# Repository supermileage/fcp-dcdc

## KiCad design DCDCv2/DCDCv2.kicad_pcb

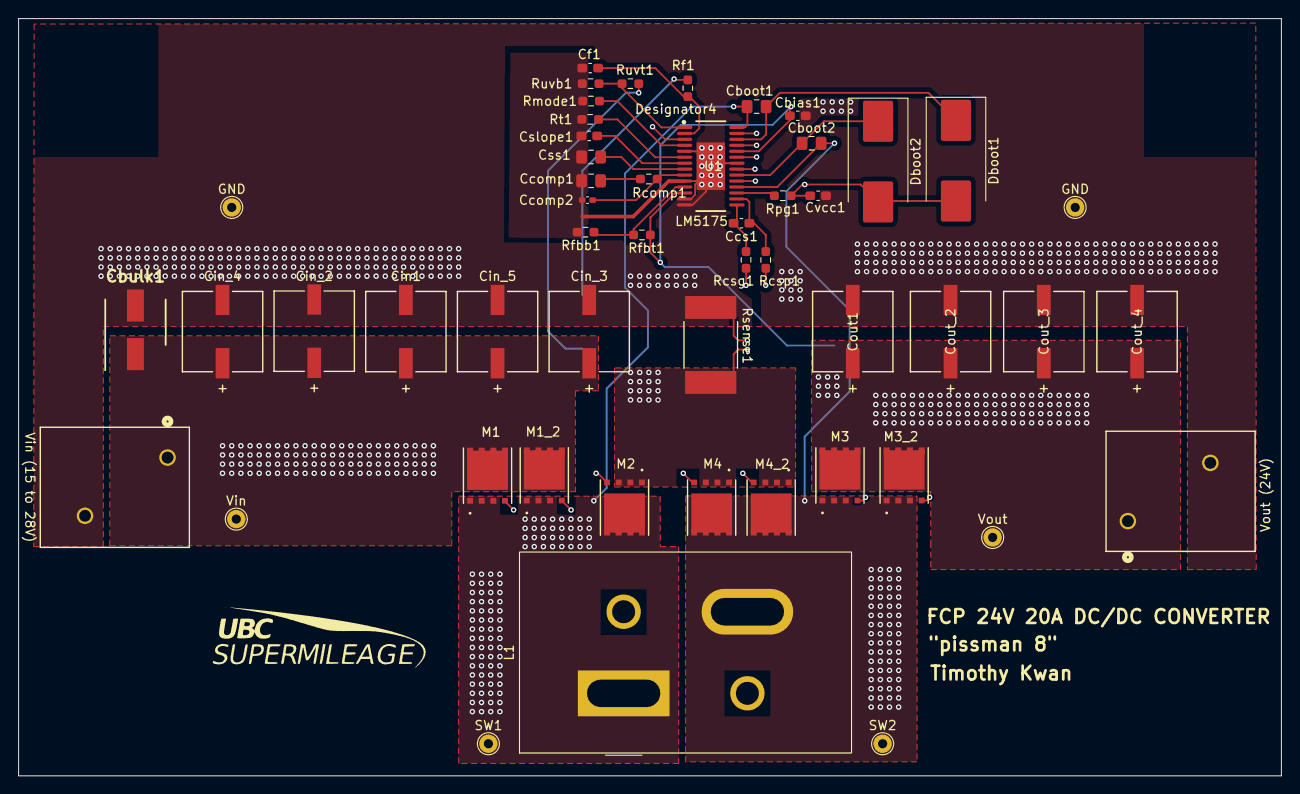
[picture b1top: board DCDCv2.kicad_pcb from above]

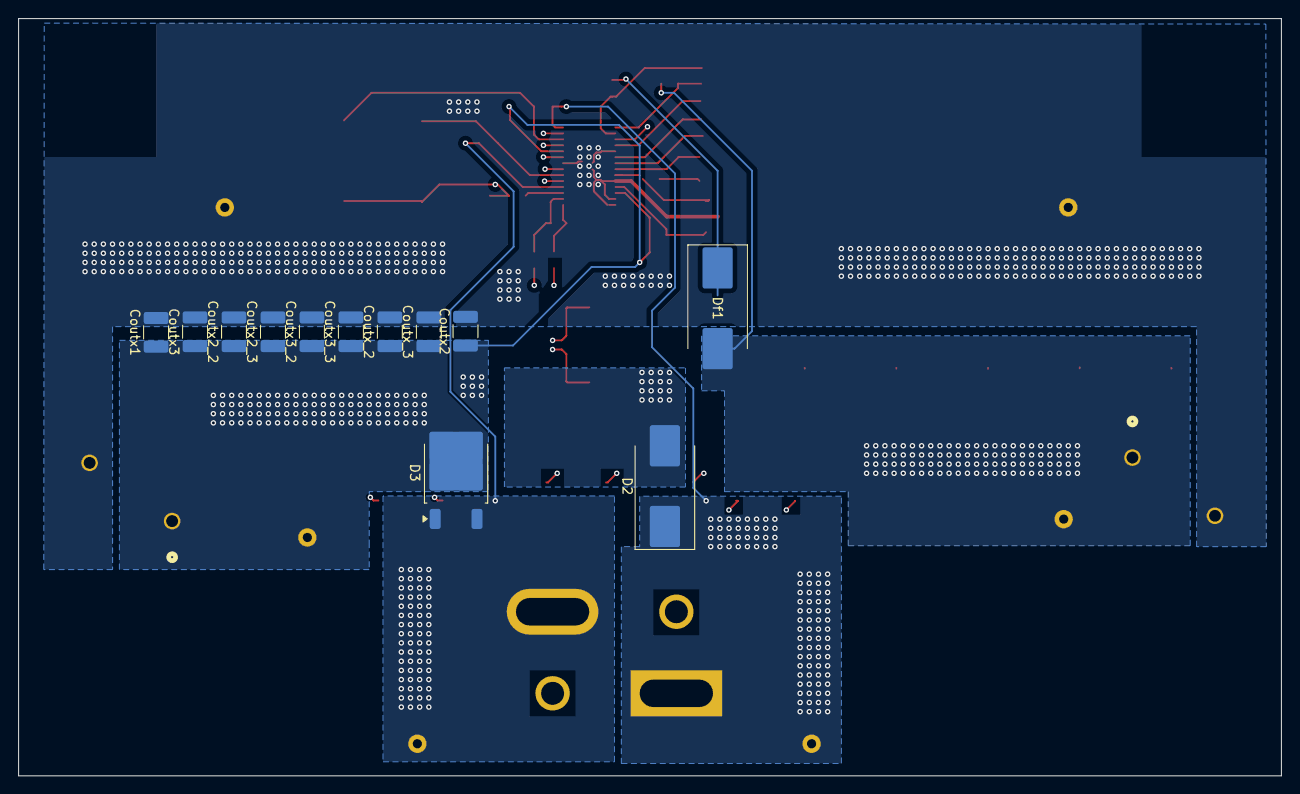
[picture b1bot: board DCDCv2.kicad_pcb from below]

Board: 4 copper layers, 137.8 x 82.6 mm, 63 parts (12 on the bottom side), 26 nets.

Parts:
Cbias1: C1608X5R1H105K080AB; C_0603_1608Metric_Pad1.08x0.95mm_HandSolder
Cboot1, Cboot2: 08053C104JAZ2A; C_0805_2012Metric_Pad1.18x1.45mm_HandSolder
Cbulk1: UUD1V680MCL1GS; CAPAE660X800N
Ccomp1: C2012C0G1H153J085AA; C_0805_2012Metric_Pad1.18x1.45mm_HandSolder
Ccomp2: CL05C681JB5NNNC; C_0402_1005Metric_Pad0.74x0.62mm_HandSolder
Ccs1: 06035A470JAT2A; C_0603_1608Metric_Pad1.08x0.95mm_HandSolder
Cf1: C1608X5R1H224K080AB; C_0603_1608Metric_Pad1.08x0.95mm_HandSolder
Cin1: 50SVPF39M; PCAP_SVP_E12_PAN
Cin_2, Cin_3, Cin_4, Cin_5: 50SVPF39M; PCAP_SVP_E12_PAN
Cout1: 35SVPF82M
Cout_2, Cout_3, Cout_4: 35SVPF82M
Coutx1, Coutx3, Coutx3_2, Coutx3_3: GRM32ER71H106MA12; C_1210_3225Metric_Pad1.33x2.70mm_HandSolder
Coutx2, Coutx2_2, Coutx2_3: C5750X7R2E684M; C_1210_3225Metric_Pad1.33x2.70mm_HandSolder
Coutx_2, Coutx_3: GRM32ER71H106MA12; C_1210_3225Metric_Pad1.33x2.70mm_HandSolder
Cslope1: CL10C151JB8NNNC; C_0603_1608Metric_Pad1.08x0.95mm_HandSolder
Css1: CGA4J2C0G1H223J125AA; C_0805_2012Metric_Pad1.18x1.45mm_HandSolder
Cvcc1: EMK107B7105KA-T; C_0603_1608Metric_Pad1.08x0.95mm_HandSolder
D2: SL44-E3/57T; D_SMC_Handsoldering
D3: SBRD10200TR; TO-252-2
Dboot1, Dboot2: SL44-E3/57T; D_SMC_Handsoldering
Df1: SL44-E3/57T; D_SMC_Handsoldering
GND: TestPoint_THTPad_D2.0mm_Drill1.0mm
GND#2: TestPoint_THTPad_D2.0mm_Drill1.0mm
L1: GENERIC_INDUCTOR; L_Wurth_WE-HCFT-3521
M1, M1_2: CSD18513Q5A; 8power tdfn
M2: CSD18531Q5A; 8power tdfn
M3, M3_2: CSD18533Q5A; 8power tdfn
M4, M4_2: CSD19534Q5A; 8power tdfn
Rcomp1: CRCW04024K99FKED; R_0603_1608Metric_Pad0.98x0.95mm_HandSolder
Rcsg1: CRCW0603100RFKEA; R_0603_1608Metric_Pad0.98x0.95mm_HandSolder
Rcsp1: CRCW0603100RFKEA; R_0603_1608Metric_Pad0.98x0.95mm_HandSolder
Rf1: RC0603FR-0710RL; R_0603_1608Metric_Pad0.98x0.95mm_HandSolder
Rfbb1: RC0603FR-0720KL; R_0603_1608Metric_Pad0.98x0.95mm_HandSolder
Rfbt1: RC0603FR-07576KL; R_0603_1608Metric_Pad0.98x0.95mm_HandSolder
Rmode1: RC0603FR-0793K1L; R_0603_1608Metric_Pad0.98x0.95mm_HandSolder
Rpg1: RC0603FR-0720KL; R_0603_1608Metric_Pad0.98x0.95mm_HandSolder
Rsense1: CUSTOM2; RES_WSLP3921_.002OHM_VIS
Rt1: CRCW0402267KFKED; R_0603_1608Metric_Pad0.98x0.95mm_HandSolder
Ruvb1: RC0201FR-0723K7L; R_0603_1608Metric_Pad0.98x0.95mm_HandSolder
Ruvt1: RC0201FR-07249KL; R_0603_1608Metric_Pad0.98x0.95mm_HandSolder
SW1, SW2: TestPoint_THTPad_D2.0mm_Drill1.0mm
U1: LM5175PWPR; PWP0028F_N
Vin: TestPoint_THTPad_D2.0mm_Drill1.0mm
Vin (15 to 28V): Screw_Terminal_01x02; CONN_1777545
Vout: TestPoint_THTPad_D2.0mm_Drill1.0mm
Vout (24V): Screw_Terminal_01x02; CONN_1777545

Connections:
/hdrv1: M1.4 (Gate), M1_2.4 (Gate), U1.27 (HDRV1)
/hdrv2: M3.4 (Gate), M3_2.4 (Gate), U1.19 (HDRV2)
/ldrv1: M2.4 (Gate), U1.25 (LDRV1)
/ldrv2: M4.4 (Gate), M4_2.4 (Gate), U1.21 (LDRV2)
/rcs2: D2.2 (A), M2.1 (Source), M2.2 (Source), M2.3 (Source), M4.1 (Source), M4.2 (Source), M4.3 (Source), M4_2.1 (Source), M4_2.2 (Source), M4_2.3 (Source), Rcsp1.2, Rsense1.2
/sw1: Cboot1.2, D2.1 (K), L1.1, M1.1 (Source), M1.2 (Source), M1.3 (Source), M1_2.1 (Source), M1_2.2 (Source), M1_2.3 (Source), M2.5 (Drain), SW1.1, U1.28 (SW1)
/sw2: Cboot2.2, D3.1 (A), D3.3 (A), L1.2, M3.1 (Source), M3.2 (Source), M3.3 (Source), M3_2.1 (Source), M3_2.2 (Source), M3_2.3 (Source), M4.5 (Drain), M4_2.5 (Drain), SW2.1, U1.18 (SW2)
GND: Cbias1.2, Cbulk1.2 (-), Ccomp1.2, Ccomp2.2, Cf1.2, Cin1.2 (-), Cin_2.2 (-), Cin_3.2 (-), Cin_4.2 (-), Cin_5.2 (-), Cout1.2 (-), Cout_2.2 (-), Cout_3.2 (-), Cout_4.2 (-), Coutx1.2, Coutx2.2, Coutx2_2.2, Coutx2_3.2, Coutx3.2, Coutx3_2.2, Coutx3_3.2, Coutx_2.2, Coutx_3.2, Cslope1.2, Css1.2, Cvcc1.2, GND.1, GND#2.1, Rcsg1.2, Rfbb1.2, Rmode1.2, Rsense1.1, Rt1.2, Ruvb1.2, U1.5 (DITH), U1.10 (AGND), U1.13 (ISNS-), U1.14 (ISNS+), U1.22 (PGND), U1.29 (PAD), Vin (15 to 28V).2, Vout (24V).2
unnamed: Ccomp1.1, Rcomp1.2
unnamed: Cvcc1.1, Dboot1.2 (A), Dboot2.2 (A), Rpg1.1, U1.23 (VCC)
unnamed: Cboot1.1, Dboot1.1 (K), U1.26 (BOOT1)
unnamed: Cboot2.1, Dboot2.1 (K), U1.20 (BOOT2)
unnamed: Df1.1 (K), Rf1.1
unnamed: Ccomp2.1, Rcomp1.1, U1.9 (COMP)
unnamed: Ccs1.1, Rcsp1.1, U1.16 (CS)
unnamed: Ccs1.2, Rcsg1.1, U1.15 (CSG)
unnamed: Ruvb1.1, Ruvt1.2, U1.1 (EN)
unnamed: Rfbb1.1, Rfbt1.2, U1.11 (FB)
unnamed: Rmode1.1, U1.4 (MODE)
unnamed: Rpg1.2, U1.17 (PGOOD)
unnamed: Rt1.1, U1.6 (RT_SYNC)
unnamed: Cslope1.1, U1.7 (SLOPE)
unnamed: Css1.1, U1.8 (SS)
unnamed: Cf1.1, Rf1.2, U1.2 (VIN)
Vin: Cbulk1.1 (+), Cin1.1 (+), Cin_2.1 (+), Cin_3.1 (+), Cin_4.1 (+), Cin_5.1 (+), Df1.2 (A), M1.5 (Drain), M1_2.5 (Drain), Ruvt1.1, U1.3 (VINSNS), Vin.1, Vin (15 to 28V).1
Vout: Cbias1.1, Cout1.1 (+), Cout_2.1 (+), Cout_3.1 (+), Cout_4.1 (+), Coutx1.1, Coutx2.1, Coutx2_2.1, Coutx2_3.1, Coutx3.1, Coutx3_2.1, Coutx3_3.1, Coutx_2.1, Coutx_3.1, D3.2 (K), M3.5 (Drain), M3_2.5 (Drain), Rfbt1.1, U1.12 (VOSNS), U1.24 (BIAS), Vout.1, Vout (24V).1

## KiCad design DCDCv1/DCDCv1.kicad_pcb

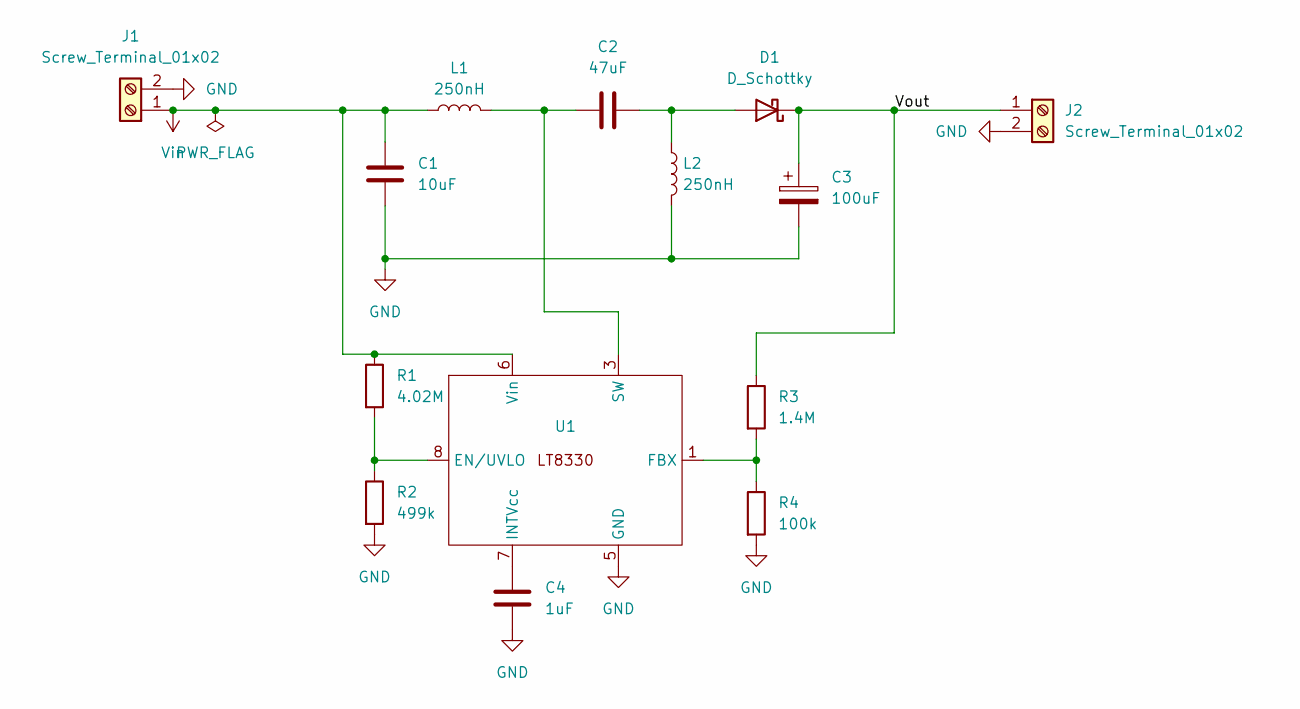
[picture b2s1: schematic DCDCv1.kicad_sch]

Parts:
C1: 10uF; C_0805_2012Metric_Pad1.18x1.45mm_HandSolder
C2: 47uF; C_2220_5750Metric_Pad1.97x5.40mm_HandSolder
C3: 100uF; CAPC6050X550N
C4: 1uF; C_0603_1608Metric_Pad1.08x0.95mm_HandSolder
D1: D_Schottky; D2PAK_STM
J1, J2: Screw_Terminal_01x02; 691137710002
L1, L2: 250nH; AVR1F131309SR25LT
R1: 4.02M; R_0805_2012Metric_Pad1.20x1.40mm_HandSolder
R2: 499k; R_0805_2012Metric_Pad1.20x1.40mm_HandSolder
R3: 1.4M; R_0603_1608Metric_Pad0.98x0.95mm_HandSolder
R4: 100k; R_0603_1608Metric_Pad0.98x0.95mm_HandSolder
U1: DFN-8_DDB

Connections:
/Vout: C3.1, D1.1 (K), J2.1, R3.1
GND: C1.2, C3.2, C4.2, J1.2, J2.2, L2.2, R2.2, R4.2, U1.5 (GND)
unnamed: C2.2, D1.2 (A), L2.1
unnamed: R1.2, R2.1, U1.8 (EN/UVLO)
unnamed: R3.2, R4.1, U1.1 (FBX)
unnamed: C4.1, U1.7 (INTVcc)
unnamed: C2.1, L1.2, U1.3 (SW)
Vin: C1.1, J1.1, L1.1, R1.1, U1.6 (Vin)

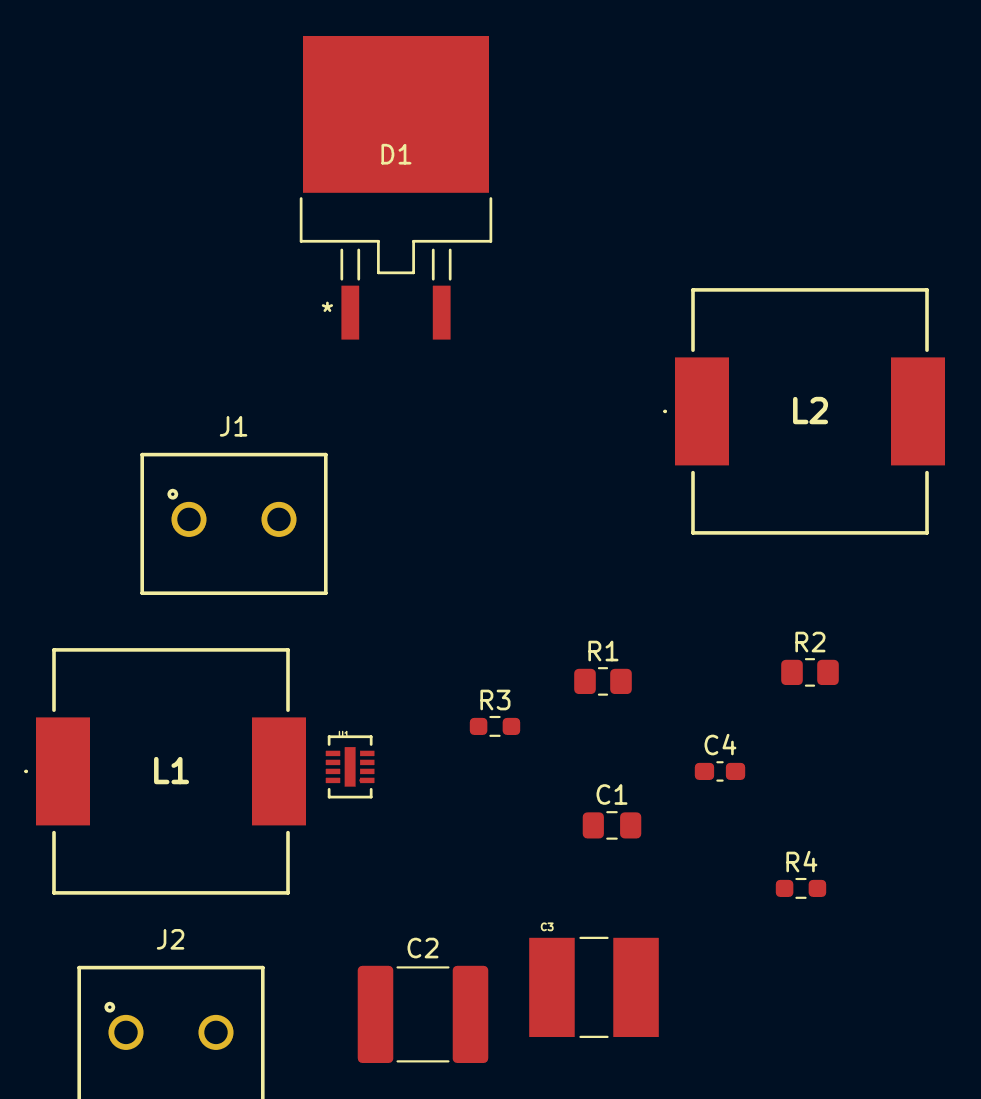
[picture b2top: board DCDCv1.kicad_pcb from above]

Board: 2 copper layers, 14 parts (0 on the bottom side), 8 nets.

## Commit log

2024-11-02 First commit, LTspice simulation added
2024-11-30 buckboost simulation and schematic added
2024-12-07 added footprints and datasheets to some components
2024-12-07 added project specific mosfet and cap library
2024-12-20 specced more components and added some cap footprints
2024-12-30 specced more components (dec 29 2024)
2024-12-31 finished speccing components in schematic
2025-01-05 preliminary pcb layout finished
2025-01-05 added 3d models for capacitors
2025-01-08 not much changed since last commit
2025-01-09 changed sw1 and sw2 to BCu layer
2025-01-13 finished PCB layout
2025-01-14 final touches, ready for order
2025-01-14 made gerber and drill files
